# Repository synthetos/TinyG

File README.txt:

ALDEN edit the README.txt to say what you think it should say.  Perhaps license info?

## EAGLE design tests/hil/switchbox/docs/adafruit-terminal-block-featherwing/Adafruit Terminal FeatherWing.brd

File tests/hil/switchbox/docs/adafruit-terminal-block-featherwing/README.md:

## Adafruit Terminal Block FeatherWing PCB
<a href="http://www.adafruit.com/products/2926"><br/>
Click here to purchase one from the Adafruit shop</a>

The Terminal Block Breakout FeatherWing kit is like the Golden Eagle of prototyping FeatherWings (eg. majestic, powerful, good-looking). To start, you get a nice prototyping area underneath your Feather, with extra pads for ground, 3.3V and SDA/SCL. Not one to stop there, we expanded the PCB out to 2" x 2.5" with 3.5mm pitch terminal blocks down each side. There's also four mounting holes so you can attach the breakout to your enclosure or project.

This product works with all our Feathers! The terminal blocks allow you to connect to any of the external Feather pins, great for wiring temporary or permanent installations. We also give you a few extra terminal block pins for ground and 3.3V connections since those are so useful.

Finally, there's a slide switch, which connects the EN pin to ground when in the 'off' position, cutting off the 3.3V regulator. Note that the FONA Feather uses both VBat and 3.3V as power supplies so you wont be able to fully turn off the FONA Feather with this switch.

PCB files for Adafruit Terminal Block FeatherWing. The format is EagleCAD schematic and board layout
- http://www.adafruit.com/products/2926

### License

Adafruit invests time and resources providing this open source design, please support Adafruit and open-source hardware by purchasing products from [Adafruit](https://www.adafruit.com)!

All text above must be included in any redistribution

Designed by Limor Fried/Ladyada for Adafruit Industries.
Creative Commons Attribution/Share-Alike, all text above must be included in any redistribution. 
See license.txt for additional information.

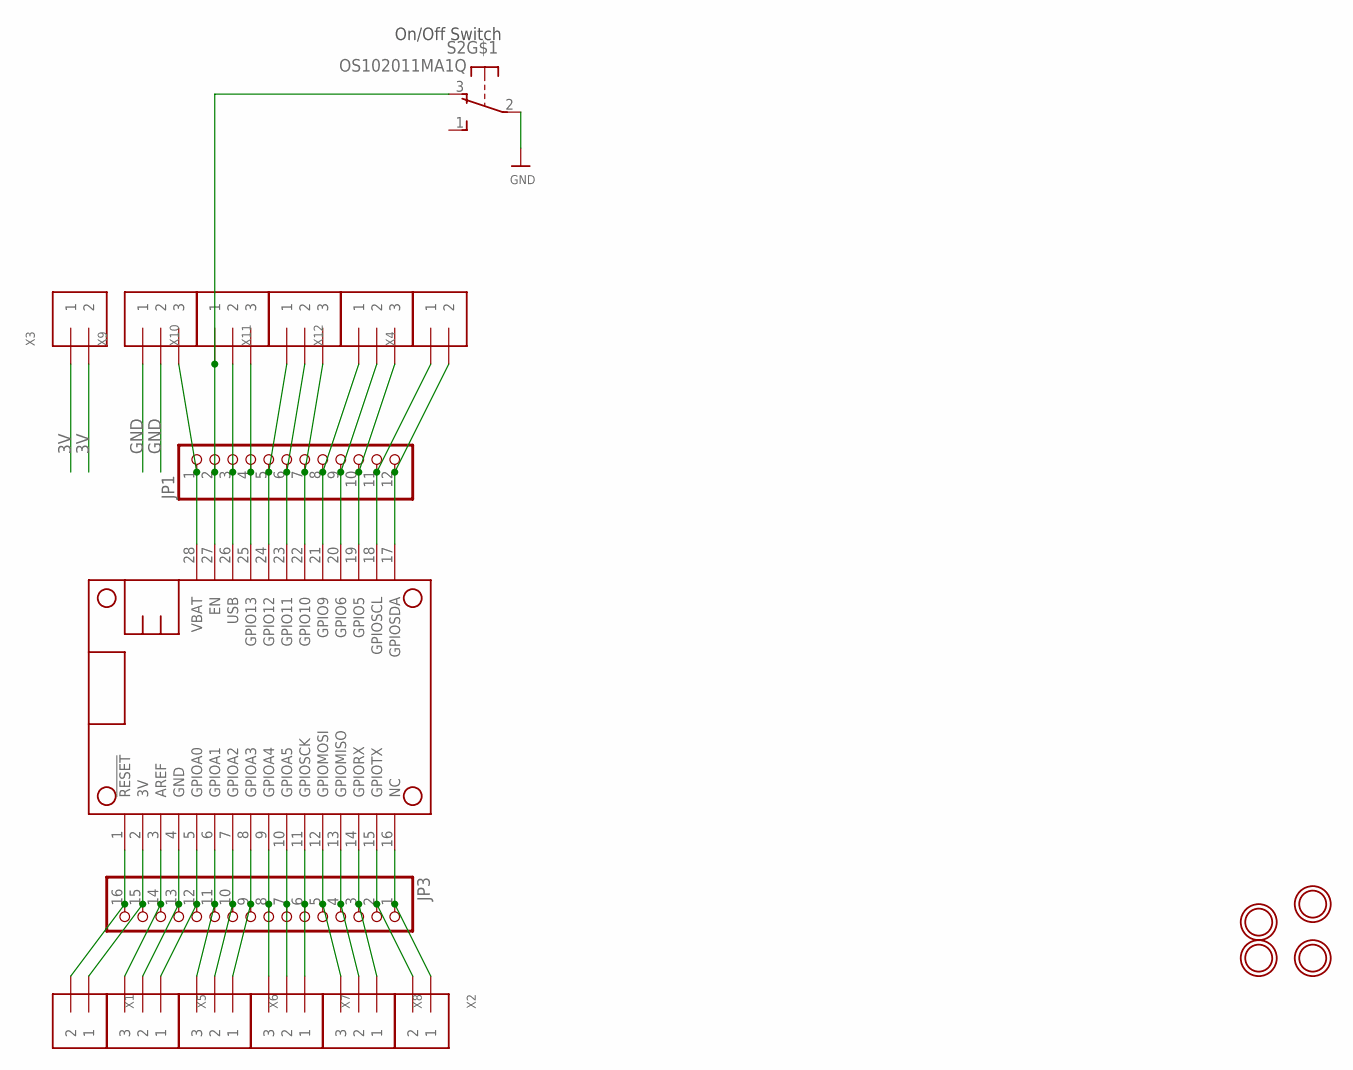
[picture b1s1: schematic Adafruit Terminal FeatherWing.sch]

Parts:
JP1: HEADER-1X1276MIL; 1X12_ROUND_76MIL
JP3: HEADER-1X16_76MIL; 1X16_ROUND_76MIL
MS1: FEATHERWING_NODIM; FEATHERWING_DIM
S2: OS102011MA1Q
U$2, U$3, U$4, U$5: MOUNTINGHOLE3.0THIN; MOUNTINGHOLE_3.0_PLATEDTHIN
X1, X2, X3, X4: TERMBLOCK_1X2; TERMBLOCK_1X2-3.5MM
X5, X6, X7, X8, X9, X10, X11, X12: TERMBLOCK_1X3; TERMBLOCK_1X3-3.5MM

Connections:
3V: JP3.15, MS1.2 (3V), X1.1, X3.1, X3.2
AREF: JP3.14, MS1.3 (AREF), X5.3
ENABLE: JP1.2, MS1.27 (EN), S2.3 (O), X10.1
GND: JP3.13, MS1.4 (GND), S2.2, X5.2, X9.1, X9.2
unnamed: JP3.1, MS1.16 (NC), X2.1
unnamed: JP1.4, MS1.25 (GPIO13), X10.3
unnamed: JP3.2, MS1.15 (GPIOTX), X2.2
unnamed: JP1.5, MS1.24 (GPIO12), X11.1
unnamed: JP3.3, MS1.14 (GPIORX), X8.1
unnamed: JP3.4, MS1.13 (GPIOMISO), X8.2
unnamed: JP3.5, MS1.12 (GPIOMOSI), X8.3
unnamed: JP3.6, MS1.11 (GPIOSCK), X7.1
unnamed: JP3.7, MS1.10 (GPIOA5), X7.2
unnamed: JP3.8, MS1.9 (GPIOA4), X7.3
unnamed: JP3.9, MS1.8 (GPIOA3), X6.1
unnamed: JP3.10, MS1.7 (GPIOA2), X6.2
unnamed: JP3.11, MS1.6 (GPIOA1), X6.3
unnamed: JP3.12, MS1.5 (GPIOA0), X5.1
unnamed: JP3.16, MS1.1 (!RESET), X1.2
unnamed: JP1.6, MS1.23 (GPIO11), X11.2
unnamed: JP1.7, MS1.22 (GPIO10), X11.3
unnamed: JP1.8, MS1.21 (GPIO9), X12.1
unnamed: JP1.9, MS1.20 (GPIO6), X12.2
unnamed: JP1.10, MS1.19 (GPIO5), X12.3
SCL: JP1.11, MS1.18 (GPIOSCL), X4.1
SDA: JP1.12, MS1.17 (GPIOSDA), X4.2
USB: JP1.3, MS1.26 (USB), X10.2
VBAT: JP1.1, MS1.28 (VBAT), X9.3

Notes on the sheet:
On/Off Switch

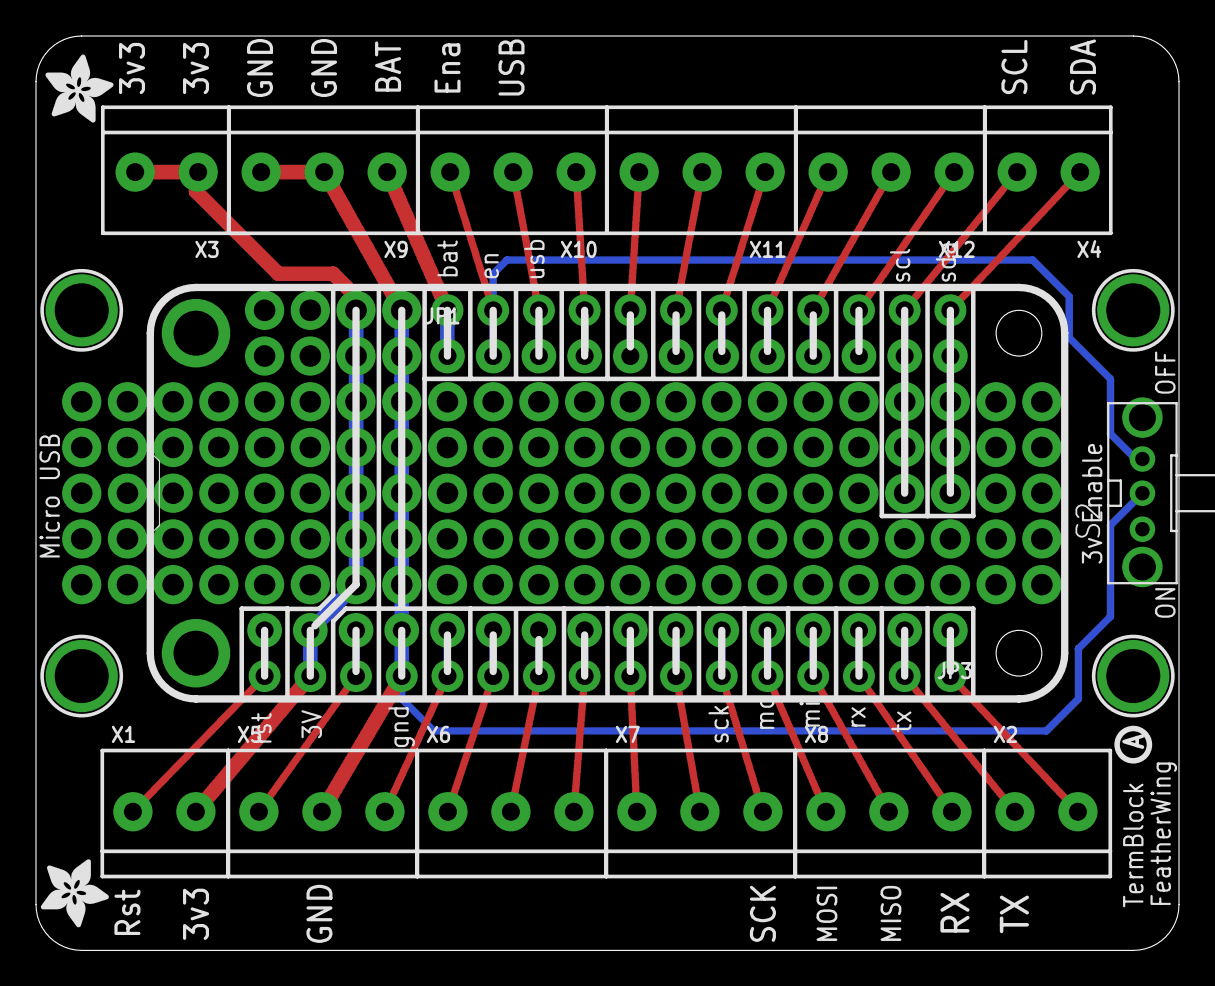
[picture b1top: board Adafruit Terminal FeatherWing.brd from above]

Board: 2 copper layers, 63.5 x 50.8 mm, 23 parts (0 on the bottom side), 28 nets.

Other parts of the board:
U$6: PCBFEAT-REV-040
U$7, U$8: ADAFRUIT_3.5MM
